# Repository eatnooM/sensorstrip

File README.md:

# sensorstrip

License: CC BY-SA 4.0

An IR LED emitter setup, for use with the Wii or IR-based light guns with a focus on remaining as slim as possible, with no components on the back of the board to allow mounting directly to a display

## Board

Grab the gerbers from [the latest release](https://github.com/eatnooM/sensorstrip/releases/latest) and upload to your favourite PCB fab ([OSHPark](https://oshpark.com/), [Aisler](https://aisler.net/), [JLCPCB](https://jlcpcb.com/)). Default settings should be fine - I wouldn't recommend getting the boards any thinner than 1.6mm as may restrict your mounting options.

HASL is a-ok to use and generally the cheapest option, so would recommend this as the surface finish.

## Assembly

### Tools required
- Soldering iron
- Solder (recommend relatively thin solder - this will make it easier to avoid bridging pins by adding too much)
- Flux (will help keep your joints shiny and happy)
- Tweezers
- Wire crimping tool (if not buying preassembled cables)

Assembly is possible with just an iron, but be super sure to get the USB-C and Molex Picoblade connectors correctly aligned before you tin more than one pad - they're tricky to fix mistakes on without hot air or a hot plate.

### What do I need?

There are a few options that will work for any given setup but I'll outline the ones most likely to be appealing

Wii / 2IR light guns only:
- 1x [power-emitter](/sensorstrip-power-emitter) + 1x [emitter](/sensorstrip-emitter)
- 1x [power-4ir](/sensorstrip-power-4ir) + 2x [emitter](/sensorstrip-emitter) (you can skip populating 2 Picoblade connectors)

4IR light guns only (Gun4IR / OpenFIRE):
- 1x [power-emitter](/sensorstrip-power-emitter) + 3x [emitter](/sensorstrip-emitter)
- 1x [power-4ir](/sensorstrip-power-4ir) + 4x [emitter](/sensorstrip-emitter)

Wii / 2IR light guns *and* 4IR light guns in square layout (OpenFIRE):
- 1x [power-42-square](/sensorstrip-power-42-square) + 4x [emitter](/sensorstrip-emitter)

Wii / 2IR light guns *and* 4IR light guns in diamond layout (Gun4IR):
- 1x [power-42-diamond](/sensorstrip-power-42-diamond) + 6x [emitter](/sensorstrip-emitter)

### Steps - Wii Sensor bar (power-emitter + emitter)

I swear I'll flesh this out later but here's how I'd go about soldering up the simplest setup of power-emitter + emitter. Any other setup is basically more of the same.

- First, solder the USB connector to J1 onto the power-emitter board. If using an iron, I'd tin one of the outer pads and move the port into place while keeping this molten (without lingering too long, of course!) - Once you're happy with the alignment, add a little solder to the other pads. Be sure plenty to get good strong joints on the shielding - these will be providing the bulk of the mechanical strength keeping the port in place. If you bridge any pads, try adding some flux and introducing a nice clean iron tip.
- Add the Molex connectors to both boards - J2 on the power-emitter, J1 on the emitter. Similar to the USB port, I've had most success lining up one of the pads, then once aligned properly move onto the mounting points and then the remaining pad.
	- You don't need to populate J2 on an emitter board unless you're connecting additional emitters through it
	- In this revision, emitter boards have swapped polarity between the 'Power in' and 'Power out' Picoblade connectors; this is to ensure you can use the pre-made cable assemblies that do not cross over the wires. If you choose to crimp your own cables, be sure to account for this.
- Add the resistors, and the F1 on the power-emitter board. Tin a single pad and introduce the component, then add solder to the other side. If you're using a tip with significant thermal mass, don't hang about for long; you may melt the solder on the other side _through_ the component. An 0603 resistor will happily float away with the surface tension on your iron and make a new home on it.
	- I'd strongly recommend populating R2 and R3 (5.1K) on the power-emitter board as they'll allow USB C to C cables to be used but if this isn't important to you, feel free to omit them.
- Add the LEDs. The LEDs can be soldered flat against the board so they stick out of the front (recommended when mounting under a display), or through-hole (can help if mounting emitters around the edge of a really thin display). The pad labelled with an A is for the anode (positive) leg. If you're using LEDs with a shallow viewing angle, you may want to angle the outer LEDs slightly to increase effective viewing angles but the SFH 4547 are fine firing straight outwards.
- Lastly, add the switch to the power-emitter board. Handily, orientation does not matter!
	- Alternatively, you can bridge the jumper J1 with a blob of solder to force the board to be always on when plugged in. If you anticipate a total power draw over over 600mA, you might want to do this as you'd be exceeding the switch's rating otherwise (300mA per pole - they're both tied together on this PCB).

Once you're done, plug in your cable between the Power out of the power-emitter board and the Power in on the emitter anddddd fingers crossed, you have light! The IR LEDs in the BOM aren't visible to the naked eye, so you may want to use a phone to test (I've heard iPhones like to filter IR out, though)

## Shells

If you want a nice enclosure to keep things looking tidy, RayneX has made [some brilliant shells](https://www.printables.com/model/1063020-sensorstrip-led-emitter-shell-for-openfire-gun4ir) on Printables.

There are enclosures for the emitter boards and the power-42-square board (which should also fit the latest revision of the power-4ir board, but this is untested at present).

## TODO
- Take some nice pictures of common setups
- Video showing assembly? Ugh

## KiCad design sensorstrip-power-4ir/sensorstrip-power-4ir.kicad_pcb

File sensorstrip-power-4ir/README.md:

# sensorstrip-power-4ir

A board that will take 5V from its USB-C board to and pass it on to all 4 emitters, with an on-off switch.

_Old picture - there have been some changes since this picture_

These boards are ideal if you only ever plan to use the emitters with light guns.

## BOM

| Reference | Part desc / number | Notes |
|----------|-------------|-------|
| J1 | 6-pin SMD Type C connector - [Mouser](https://www.mouser.co.uk/ProductDetail/GCT/USB4135-GF-A?qs=Li%252BoUPsLEnt6HRo6RUvaXA%3D%3D) / [LCSC](https://lcsc.com/product-detail/USB-Connectors_DEALON-USB-TYPE-C-007_C2927027.html) |  |
| J2-J5 | Molex 53261-0271  - [Mouser](https://www.mouser.com/ProductDetail/Molex/53261-0271?qs=%252B72YyncTwW%252B8%252BBjraxGf3A%3D%3D) | |
| - | Picoblade Cable assembly - [Preassembled - Mouser (60cm length)](https://www.mouser.com/ProductDetail/Molex/15134-0206?qs=F%2F1Z9SgJL%252BXkfyBT%252BHsQcw%3D%3D) / [LCSC - housing](https://www.lcsc.com/product-detail/_MOLEX-_C293613.html) + [LCSC - terminal](https://www.lcsc.com/product-detail/_MOLEX-_C259763.html) | Need one of these for each emitter board |
| F1 | 0805 PTC - [Mouser](https://www.mouser.com/ProductDetail/Murata-Electronics/PRG21BC0R2MM1RA?qs=makukexe9nzHJ%252Bvxp0S09w%3D%3D) / [LCSC](https://www.lcsc.com/product-detail/_Murata-Electronics-_C184863.html) | Overcurrent protection |
| D1 | Status LED - [Mouser](https://www.mouser.co.uk/ProductDetail/Wurth-Elektronik/150060GS75000?qs=LlUlMxKIyB0UYkq5lDO8nA%3D%3D) / [LCSC](https://www.lcsc.com/product-detail/Light-Emitting-Diodes-LED_Everlight-Elec-19-217-GHC-YR1S2-3T_C72043.html) | Optional |
| R1,R2 | 5.1K 0603 - [Mouser](https://www.mouser.com/ProductDetail/Panasonic/ERJ-3EKF5101V?qs=MVjVSMjNRMqhyossZ5oXsQ%3D%3D) / [LCSC](https://lcsc.com/product-detail/Chip-Resistor-Surface-Mount_PANASONIC-ERJ3EKF5101V_C123727.html) | Required if powering from C-C cable |
| R3 | 1K 0603 - [Mouser](https://www.mouser.co.uk/ProductDetail/Panasonic/ERJ-3EKF1001V?qs=H7k1u0Mp9JTM8yQxOuvoDg%3D%3D) / [LCSC](https://www.lcsc.com/product-detail/Chip-Resistor-Surface-Mount_YAGEO-RC0603FR-071KL_C22548.html) | Required for status LED |
| SW1 | DPDT - [Mouser](https://www.mouser.co.uk/ProductDetail/CK/JS202011SCQN?qs=LgMIjt8LuD95JYWxZ7NvZA%3D%3D) / [LCSC](https://lcsc.com/product-detail/Slide-Switches_C-K-JS202011SCQN_C221666.html) | |

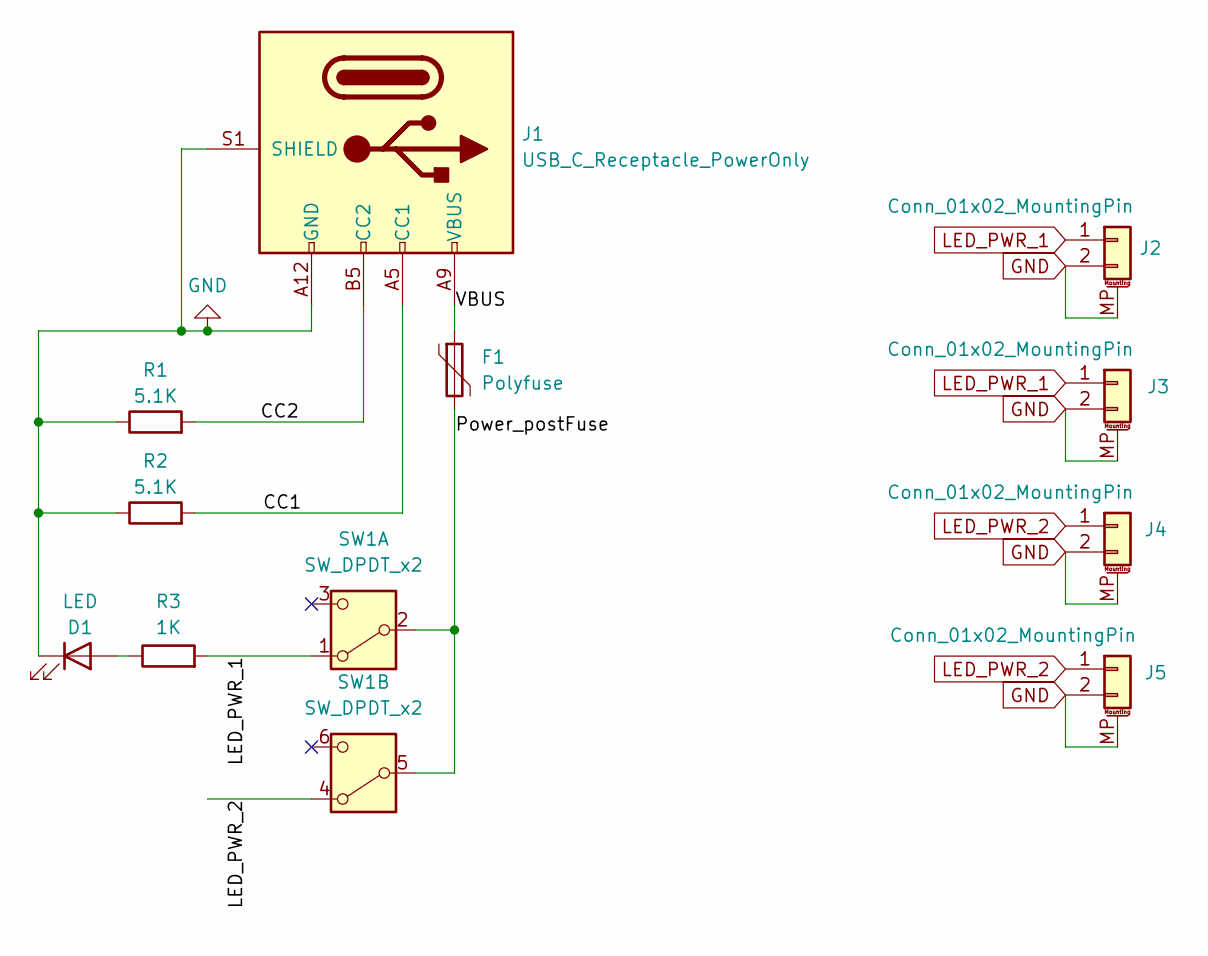
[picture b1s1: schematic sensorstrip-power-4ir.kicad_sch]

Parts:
D1: LED; LED_0603_1608Metric_Pad1.05x0.95mm_HandSolder
F1: Polyfuse; Fuse_0805_2012Metric_Pad1.15x1.40mm_HandSolder
J1: USB_C_Receptacle_PowerOnly; DEALON USB Type-C 6Pin
J2, J3, J4, J5: Conn_01x02_MountingPin; Molex_Picoblade_53261-0271-Hybrid
R1, R2: 5.1K; R_0603_1608Metric_Pad0.98x0.95mm_HandSolder
R3: 1K; R_0603_1608Metric_Pad0.98x0.95mm_HandSolder
SW1: SW_DPDT_x2; JS202011SCQN-Hybrid-12-PTH

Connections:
/CC1: J1.A5 (CC1), R2.2
/CC2: J1.B5 (CC2), R1.2
/Power_postFuse: F1.2, SW1.2 (B), SW1.5 (B)
/VBUS: F1.1, J1.A9 (VBUS), J1.B9 (VBUS)
GND: D1.1 (K), J1.A12 (GND), J1.B12 (GND), J1.S1 (SHIELD), J2.2, J2.MP (MountPin), J3.2, J3.MP (MountPin), J4.2, J4.MP (MountPin), J5.2, J5.MP (MountPin), R1.1, R2.1
LED_PWR_1: J2.1, J3.1, R3.2, SW1.1 (A)
LED_PWR_2: J4.1, J5.1, SW1.4 (A)
unnamed: D1.2 (A), R3.1

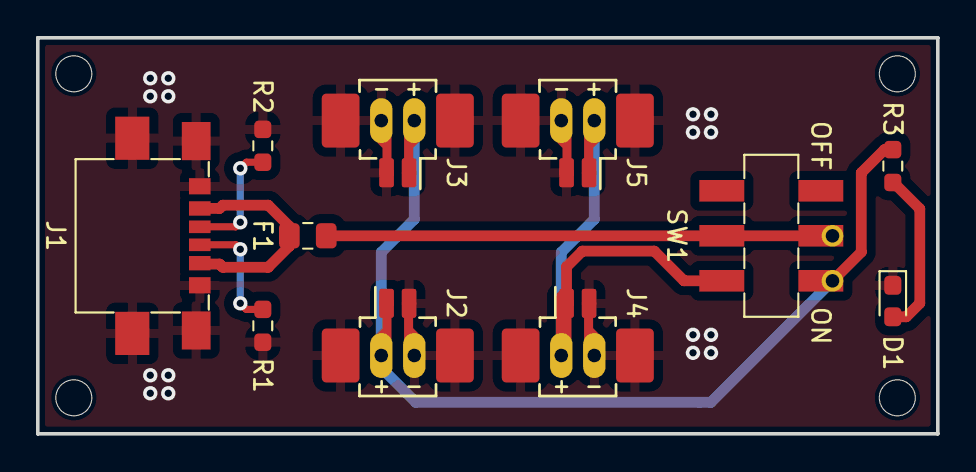
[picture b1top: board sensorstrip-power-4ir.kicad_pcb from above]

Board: 2 copper layers, 50.0 x 22.0 mm, 11 parts (0 on the bottom side), 8 nets.

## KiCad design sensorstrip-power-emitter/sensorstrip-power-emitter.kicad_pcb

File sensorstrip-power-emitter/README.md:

# sensorstrip-power-emitter

A small and elegant board that will take 5V from its USB-C board to power its own LEDs and pass it on to any other emitter boards in your setup.

Old picture - there have been some changes since this picture

This board is ideal for the smallest setup possible with no dedicated power board.

## BOM

| Reference | Part desc / number | Notes |
|----------|-------------|-------|
| J1 | 6-pin SMD Type C connector - [Mouser](https://www.mouser.co.uk/ProductDetail/GCT/USB4135-GF-A?qs=Li%252BoUPsLEnt6HRo6RUvaXA%3D%3D) / [LCSC](https://lcsc.com/product-detail/USB-Connectors_DEALON-USB-TYPE-C-007_C2927027.html) |  |
| J2 | Molex 53261-0271  - [Mouser](https://www.mouser.com/ProductDetail/Molex/53261-0271?qs=%252B72YyncTwW%252B8%252BBjraxGf3A%3D%3D) | |
| - | Picoblade Cable assembly - [Preassembled - Mouser (60cm length)](https://www.mouser.com/ProductDetail/Molex/15134-0206?qs=F%2F1Z9SgJL%252BXkfyBT%252BHsQcw%3D%3D) / [LCSC - housing](https://www.lcsc.com/product-detail/_MOLEX-_C293613.html) + [LCSC - terminal](https://www.lcsc.com/product-detail/_MOLEX-_C259763.html) | Need one of these for each emitter board |
| F1 | 0805 PTC - [Mouser](https://www.mouser.com/ProductDetail/Murata-Electronics/PRG21BC0R2MM1RA?qs=makukexe9nzHJ%252Bvxp0S09w%3D%3D) / [LCSC](https://www.lcsc.com/product-detail/_Murata-Electronics-_C184863.html) | Overcurrent protection |
| D1-3 | IR LED - 940nm - [Mouser](https://www.mouser.com/ProductDetail/720-SFH4547) |  |
| D4 | Status LED - [Mouser](https://www.mouser.co.uk/ProductDetail/Wurth-Elektronik/150060GS75000?qs=LlUlMxKIyB0UYkq5lDO8nA%3D%3D) / [LCSC](https://www.lcsc.com/product-detail/Light-Emitting-Diodes-LED_Everlight-Elec-19-217-GHC-YR1S2-3T_C72043.html) | Optional |
| R1 | 7-120R 0805 - [Mouser](https://www.mouser.com/ProductDetail/YAGEO/RC0805FR-0710RL?qs=8Y8p%252BasKcI5T5bn0nqNRsw%3D%3D) / [LCSC](https://www.lcsc.com/product-detail/Chip-Resistor-Surface-Mount_YAGEO-RC0805FR-0710RL_C96347.html) | Value depends on your LEDs - 7-10R work well with SFH-4547 |
| R2,R3 | 5.1K 0603 - [Mouser](https://www.mouser.com/ProductDetail/Panasonic/ERJ-3EKF5101V?qs=MVjVSMjNRMqhyossZ5oXsQ%3D%3D) / [LCSC](https://lcsc.com/product-detail/Chip-Resistor-Surface-Mount_PANASONIC-ERJ3EKF5101V_C123727.html) | Required if powering from C-C cable |
| R4 | 1K 0603 - [Mouser](https://www.mouser.co.uk/ProductDetail/Panasonic/ERJ-3EKF1001V?qs=H7k1u0Mp9JTM8yQxOuvoDg%3D%3D) / [LCSC](https://www.lcsc.com/product-detail/Chip-Resistor-Surface-Mount_YAGEO-RC0603FR-071KL_C22548.html) | Required for status LED |
| SW1 | DPDT - [Mouser](https://www.mouser.co.uk/ProductDetail/CK/JS202011SCQN?qs=LgMIjt8LuD95JYWxZ7NvZA%3D%3D) / [LCSC](https://lcsc.com/product-detail/Slide-Switches_C-K-JS202011SCQN_C221666.html) | Optional, but recommended |

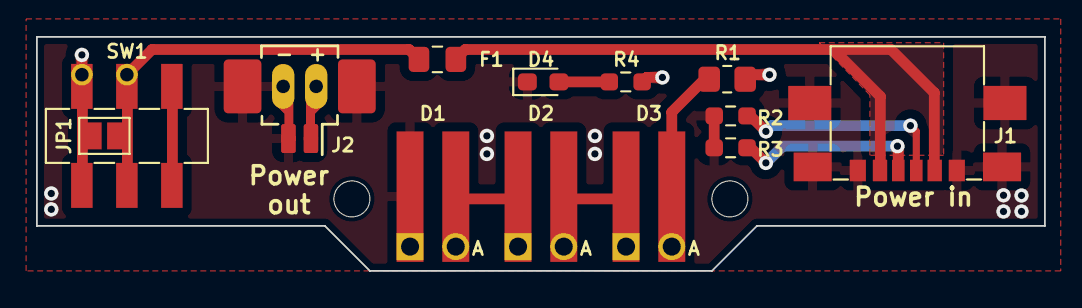
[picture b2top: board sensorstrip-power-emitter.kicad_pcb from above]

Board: 2 copper layers, 56.0 x 13.0 mm, 13 parts (0 on the bottom side), 10 nets.

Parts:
D1, D2, D3: LED; LED_THT-1.27mm-OrthogonalSMDAndTHT
D4: LED; LED_0603_1608Metric_Pad1.05x0.95mm_HandSolder
F1: Polyfuse; Fuse_0805_2012Metric_Pad1.15x1.40mm_HandSolder
J1: USB_C_Receptacle_PowerOnly; DEALON USB Type-C 6Pin
J2: Conn_01x02_MountingPin; Molex_Picoblade_53261-0271-Hybrid
JP1: SolderJumper_2_Open; SolderJumper-2_P1.3mm_Open_Pad1.0x1.5mm
R1: 10R; R_0805_2012Metric_Pad1.20x1.40mm_HandSolder
R2, R3: 5.1K; R_0603_1608Metric_Pad0.98x0.95mm_HandSolder
R4: 1K; R_0603_1608Metric_Pad0.98x0.95mm_HandSolder
SW1: SW_DPDT_x2; JS202011SCQN-Hybrid

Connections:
/CC1: J1.A5 (CC1), R2.2
/CC2: J1.B5 (CC2), R3.2
/D1+: D1.2 (A), D2.1 (K)
/D2+: D2.2 (A), D3.1 (K)
/D3+: D3.2 (A), R1.1
/Power_postFuse: F1.2, JP1.2 (B), SW1.2 (B), SW1.5 (B)
/VBUS: F1.1, J1.A9 (VBUS), J1.B9 (VBUS)
GND: D1.1 (K), D4.1 (K), J1.A12 (GND), J1.B12 (GND), J1.S1 (SHIELD), J2.2, J2.MP (MountPin), R2.1, R3.1
unnamed: D4.2 (A), R4.1
Power_postSwitch: J2.1, JP1.1 (A), R1.2, R4.2, SW1.1 (A), SW1.4 (A)

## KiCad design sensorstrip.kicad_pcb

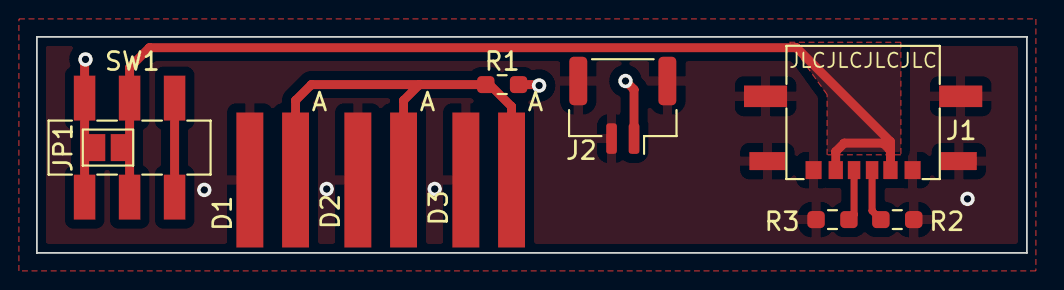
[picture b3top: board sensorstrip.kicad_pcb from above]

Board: 2 copper layers, 55.0 x 12.0 mm, 10 parts (0 on the bottom side), 6 nets.

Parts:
D1, D2, D3: LED; LED_THT-1.27mm-OrthogonalSMDMount
J1: USB_C_Receptacle_PowerOnly; DEALON USB Type-C 6Pin
J2: Conn_01x02_MountingPin; JST_GH_SM02B-GHS-TB_1x02-1MP_P1.25mm_Horizontal
JP1: SolderJumper_2_Open; SolderJumper-2_P1.3mm_Open_Pad1.0x1.5mm
R1: 120R; R_0603_1608Metric_Pad0.98x0.95mm_HandSolder
R2, R3: 5.1K; R_0603_1608Metric_Pad0.98x0.95mm_HandSolder
SW1: SW_DPDT_x2; JS202011SCQN

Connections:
/CC1: J1.A5 (CC1), R2.2
/CC2: J1.B5 (CC2), R3.2
/LEDs: D1.2 (A), D2.2 (A), D3.2 (A), R1.1
/VBUS: J1.A9 (VBUS), J1.B9 (VBUS), JP1.2 (B), SW1.2 (B), SW1.5 (B)
GND: D1.1 (K), D2.1 (K), D3.1 (K), J1.A12 (GND), J1.B12 (GND), J1.S1 (SHIELD), J2.2, J2.MP (MountPin), R2.1, R3.1
Power_postSwitch: J2.1, JP1.1 (A), R1.2, SW1.1 (A), SW1.4 (A)

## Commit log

2022-11-01 Initial commit
    Add KiCad files and gerbers
2022-11-01 Add sensorstrip-render.png
2022-11-01 Update Readme
    Add quick description and BOM
2022-11-05 Readme: Add Assembly section
2022-11-05 Clean up Assembly section
2022-11-05 Add instructions for ordering boards
2022-11-05 Clarify optional LEDs
2022-11-06 Add mounting and PCB thickness images
2022-11-06 Fix readme images
2022-11-06 Resize image
2022-11-06 Resize mounting image
2022-11-07 Update README.md
    Get distracted mid-sentence? Me? Never.
2022-11-23 Update to v3
2022-11-23 Cleanup table
2022-11-23 More readme cleanup
2022-11-23 messy messy messy
2022-11-23 more words
2022-11-25 Minor tweaks
2022-11-25 Update render
2022-11-25 Use more appropriate J2 symbol to prevent DRC warning
2022-12-03 Clean up wording
2022-12-28 Small shuffle, note V2 is now tested
2022-12-30 Update README.md
    Add link to Mister Addons for their Gun Con 3 offering
2023-02-01 v3 (for real this time):
    - Differentiate 'sender' and 'receiver' boards and allow daisy chaining receivers
    - Update LED footprint to allow for more mounting options
    - Swap to Molex Picoblade 53261 connector for ease of assembly
    - Add PTH mounting holes to allow stacking boards for larger LEDs, or mounting with screws
    - Add PPTC for overcurrent protection
2023-02-01 Fix readme
2023-02-01 Update render with v3 boards
2023-02-01 of course i ran drc before pushing what do you take me for
2023-02-01 so glad i'm squashing these on merge
2023-02-19 fix humongous oversight
2023-02-19 Update readme / board render
2023-03-25 Cleanup in preparation for push
    Update project files to KiCad 7 format
2023-03-25 v3 (#1)
    * v3 (for real this time):
    - Fix huge schematic oversight where LEDs were driven in parallel instead of series
    - Differentiate 'sender' and 'receiver' boards and allow daisy chaining receivers
    - Update LED footprint to allow for more mounting options
    - Swap to Molex Picoblade 53261 connector for ease of assembly
    - Add PTH mounting holes to allow stacking boards for larger LEDs, or mounting with screws
2023-09-14 Update BOM
2023-10-08 Update readme and images; tweak sender board CC trace width
2023-10-08 Do I look like I know what a jay peg is?
2024-04-01 Minor sensorstrip-sender revision:
    - Swap PTH for NPTH
    - Add through-holes to power switch pads for switch relocation
2024-04-07 Add 4IR+2IR switchable power board
    Minor cleanup
2024-09-29 Update README.md
    Reflect change to CC BY-SA 4.0 license
2024-10-03 Add 2IR/4IR togglable board for square layouts
2024-10-30 Update 2/4IR square board for consistent status LED behaviour
    Update DP3T switch footprint to make installing JS203011SCQN easier
    Rename 2IR/4IR diamond layout board for clarity
2024-10-30 Update 4IR-only power board:
    - Rename for clarity
    - Split IR power across poles for switch longevity
    - Add power LED
    - Use same board layout as 2IR/4IR diamond layout for compatibility
2024-10-31 Rename sender / receiver boards to power-emitter and emitter
    ...hopefully this is clearer
    Also some tidying of older boards
2024-11-01 Split documentation across the pages for each board
    Remove some rambling, add some different rambling
2024-11-03 Documentation revamp (#2)
    Split documentation across the pages for each board
    Remove some rambling, add some different rambling
2024-11-03 Add images of each board
2024-11-05 Add Shells section
2024-11-07 Update USB-C connector
    Allowances for GCT USB4135-GF-A footprint
2024-11-07 BOM additions (#3)
    Update USB-C connector
    Allowances for GCT USB4135-GF-A footprint
    Update README BOM tables with Mouser links
